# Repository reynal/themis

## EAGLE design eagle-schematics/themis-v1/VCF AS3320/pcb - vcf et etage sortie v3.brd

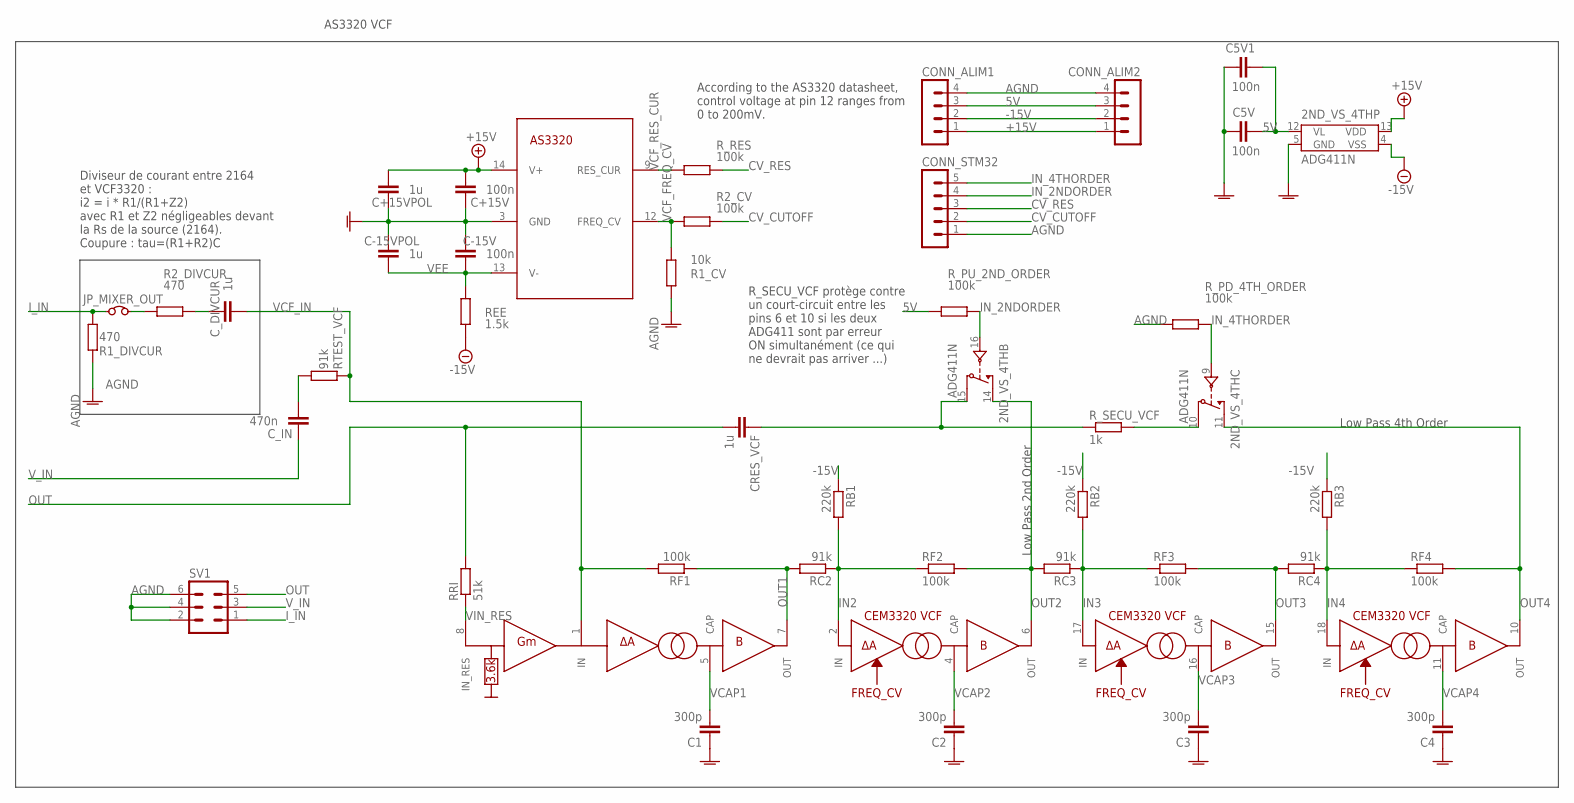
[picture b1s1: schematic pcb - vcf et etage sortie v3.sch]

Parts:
2ND_VS_4TH: ADG411N; DIL16
C1, C2, C3, C4: 300p; C075-032X103
C5V, C5V1: 100n; C075-032X103
C+15V: 100n; C075-032X103
C+15VPOL: 1u; C075-032X103
C-15V: 100n; C075-032X103
C-15VPOL: 1u; C075-032X103
CONN_ALIM1, CONN_ALIM2: MA04-1
CONN_STM32: MA05-1
CRES_VCF: 1u; C075-032X103
C_DIVCUR: 1u; C075-032X103
C_IN: 470n; C075-032X103
JP_MIXER_OUT: JUMPER_WIRE; JUMPER
R1_CV: 10k; 0204/7
R1_DIVCUR, R2_DIVCUR: 470; 0207/10
R2_CV: 100k; 0204/7
RB1: 220k; 0207/10
RB2, RB3: 220k; 0204/7
RC2, RC3, RC4: 91k; 0204/7
REE: 1.5k; 0207/10
RF1, RF3: 100k; 0207/10
RF2, RF4: 100k; 0204/7
RRI: 51k; 0207/10
RTEST_VCF: 91k; 0207/10
R_PD_4TH_ORDER: 100k; 0204/7
R_PU_2ND_ORDER: 100k; 0204/7
R_RES: 100k; 0204/7
R_SECU_VCF: 1k; 0204/7
SV1: MA03-2
VCF: AS3320; DIL18

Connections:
5V: 2ND_VS_4TH.12 (VL), C5V.1, C5V1.1, CONN_ALIM1.3, CONN_ALIM2.3, R_PU_2ND_ORDER.1
+15V: 2ND_VS_4TH.13 (VDD), C+15V.2, C+15VPOL.2, CONN_ALIM1.1, CONN_ALIM2.1, VCF.14 (V+)
-15V: 2ND_VS_4TH.4 (VSS), CONN_ALIM1.2, CONN_ALIM2.2, RB1.1, RB2.1, RB3.1, REE.1
AGND: 2ND_VS_4TH.5 (GND), C1.1, C2.1, C3.1, C4.1, C5V.2, C5V1.2, C+15V.1, C+15VPOL.1, C-15V.2, C-15VPOL.2, CONN_ALIM1.4, CONN_ALIM2.4, CONN_STM32.1, R1_CV.2, R1_DIVCUR.2, R_PD_4TH_ORDER.1, SV1.2, SV1.4, SV1.6, VCF.3 (GND)
CV_CUTOFF: CONN_STM32.2, R2_CV.2
CV_RES: CONN_STM32.3, R_RES.2
IN2: RB1.2, RC2.1, RF2.1, VCF.2 (IN)
IN3: RB2.2, RC3.1, RF3.1, VCF.17 (IN)
IN4: RB3.2, RC4.1, RF4.1, VCF.18 (IN)
IN_2NDORDER: 2ND_VS_4TH.16 (IN), CONN_STM32.4, R_PU_2ND_ORDER.2
IN_4THORDER: 2ND_VS_4TH.9 (IN), CONN_STM32.5, R_PD_4TH_ORDER.2
I_IN: JP_MIXER_OUT.1, R1_DIVCUR.1, SV1.1
unnamed: C_IN.1, RTEST_VCF.1
unnamed: 2ND_VS_4TH.15 (D), CRES_VCF.1, R_SECU_VCF.1
unnamed: 2ND_VS_4TH.10 (D), R_SECU_VCF.2
unnamed: C_DIVCUR.2, R2_DIVCUR.1
unnamed: JP_MIXER_OUT.2, R2_DIVCUR.2
OUT: CRES_VCF.2, RRI.2, SV1.5
OUT1: RC2.2, RF1.1, VCF.7 (OUT)
OUT2: 2ND_VS_4TH.14 (S), RC3.2, RF2.2, VCF.6 (OUT)
OUT3: RC4.2, RF3.2, VCF.15 (OUT)
OUT4: 2ND_VS_4TH.11 (S), RF4.2, VCF.10 (OUT)
VCAP1: C1.2, VCF.5 (CAP)
VCAP2: C2.2, VCF.4 (CAP)
VCAP3: C3.2, VCF.16 (CAP)
VCAP4: C4.2, VCF.11 (CAP)
VCF_FREQ_CV: R1_CV.1, R2_CV.1, VCF.12 (FREQ_CV)
VCF_IN: C_DIVCUR.1, RF1.2, RTEST_VCF.2, VCF.1 (IN)
VCF_RES_CUR: R_RES.1, VCF.9 (RES_CUR)
VEE: C-15V.1, C-15VPOL.1, REE.2, VCF.13 (V-)
VIN_RES: RRI.1, VCF.8 (IN_RES)
V_IN: C_IN.2, SV1.3

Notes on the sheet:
According to the AS3320 datasheet, control voltage at pin 12 ranges from 0 to 200mV.
Diviseur de courant entre 2164 et VCF3320 : i2 = i * R1/(R1+Z2) avec R1 et Z2 négligeables devant la Rs de la source (2164). Coupure : tau=(R1+R2)C
AS3320 VCF
R_SECU_VCF protège contre un court-circuit entre les pins 6 et 10 si les deux ADG411 sont par erreur ON simultanément (ce qui ne devrait pas arriver ...)
Low Pass 2nd Order
Low Pass 4th Order

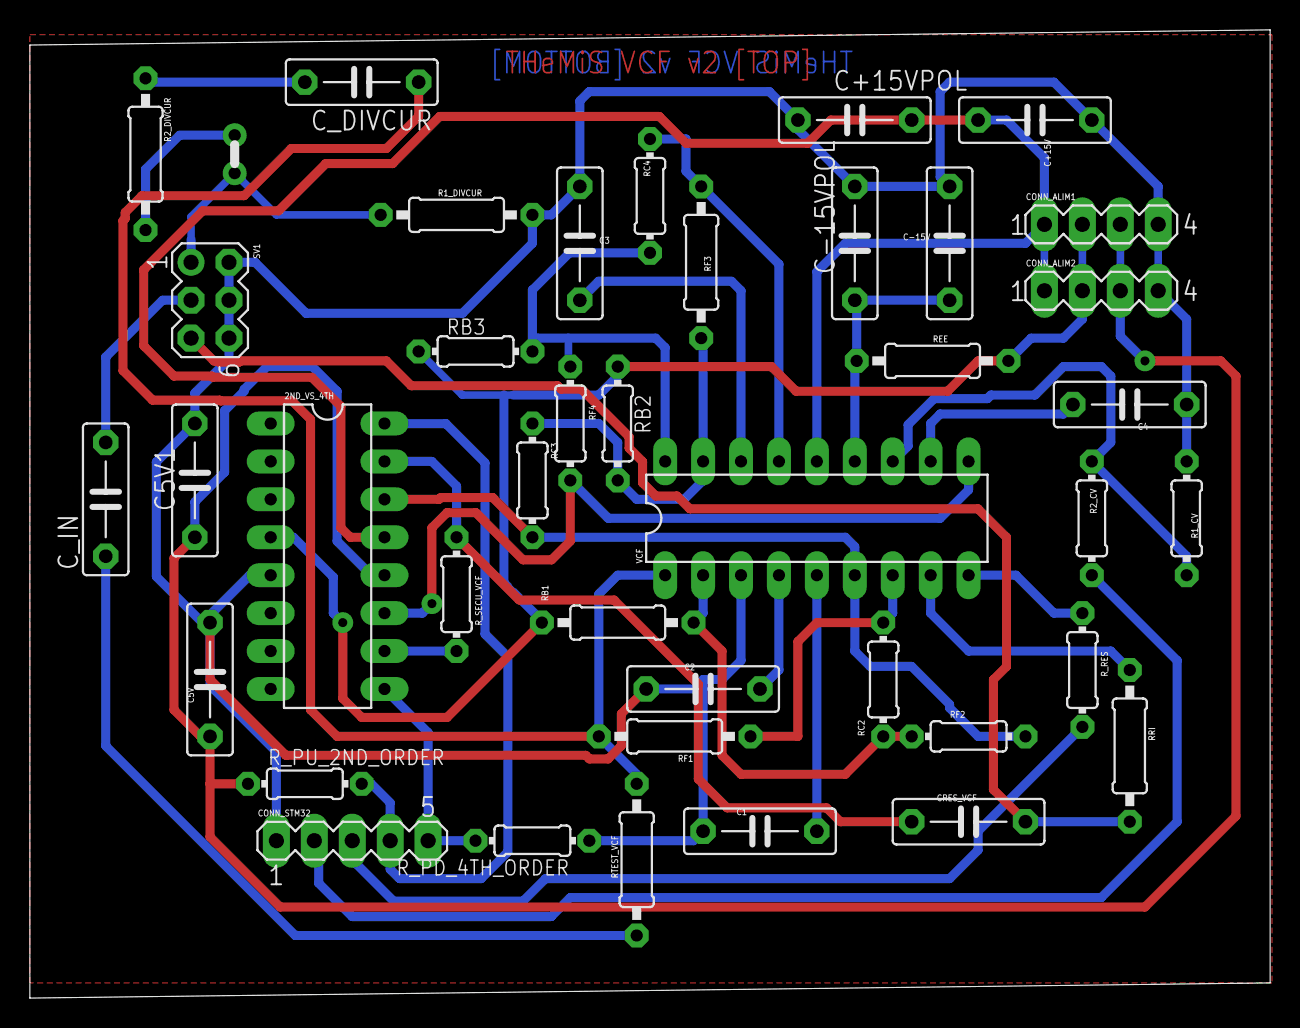
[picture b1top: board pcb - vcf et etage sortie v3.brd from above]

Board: 2 copper layers, 83.1 x 64.8 mm, 41 parts (0 on the bottom side), 32 nets.

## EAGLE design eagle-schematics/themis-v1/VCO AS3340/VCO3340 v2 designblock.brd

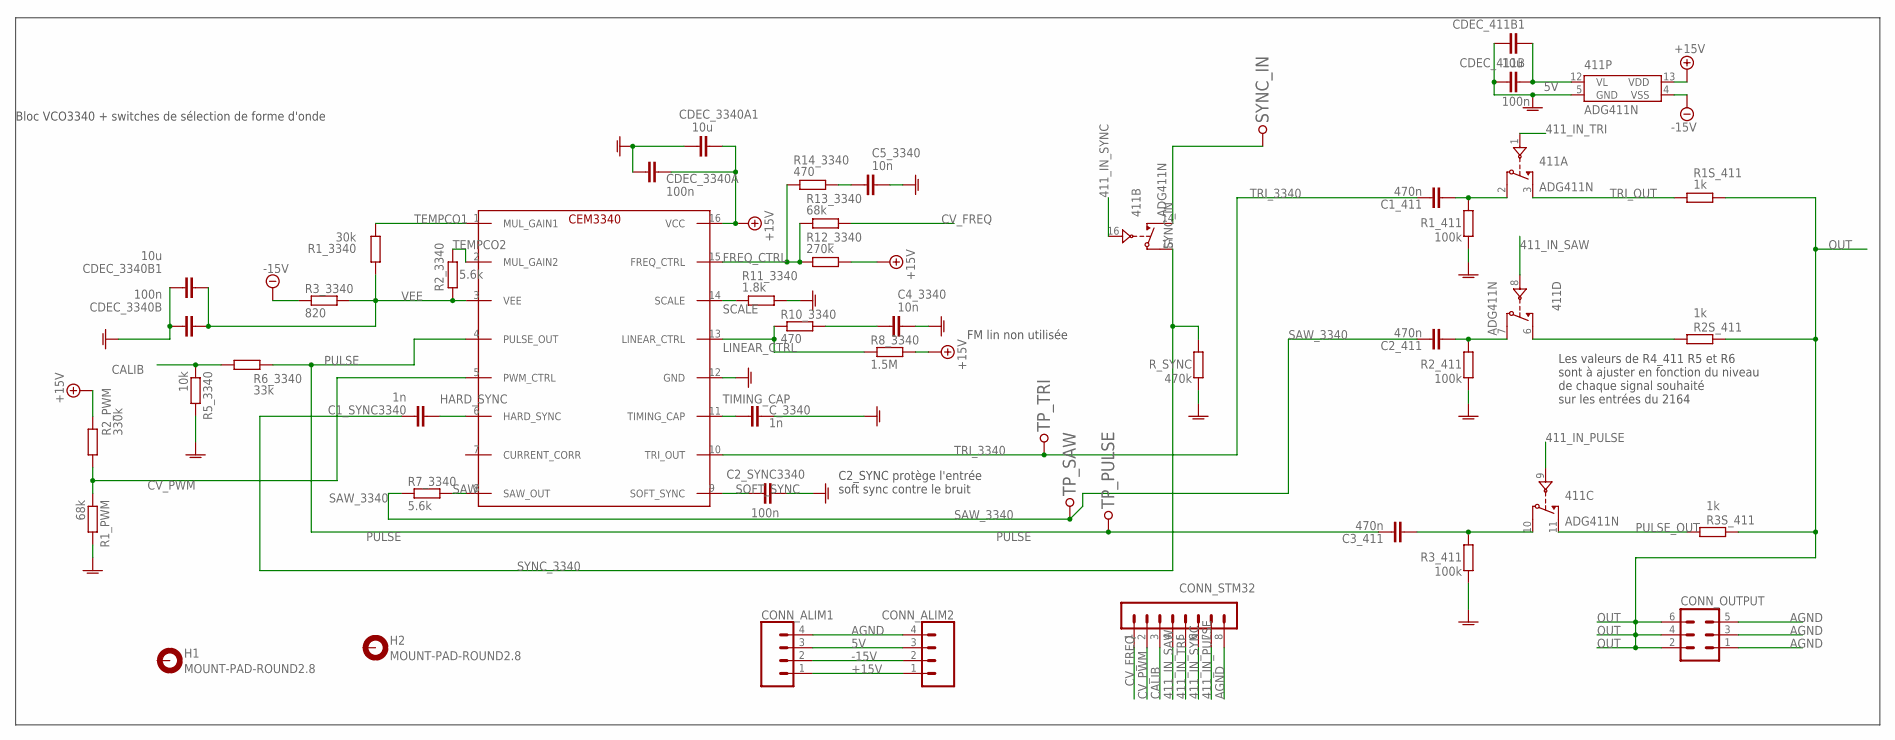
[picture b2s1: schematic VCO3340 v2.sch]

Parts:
411: ADG411N; DIL16
C1_411, C2_411: 470n; C075-032X103
C1_SYNC3340: 1n; C075-032X103
C2_SYNC3340: 100n; C075-032X103
C3_411: 470n; C102-043X133
C4_3340: 10n; C050-025X075
C5_3340: 10n; C075-032X103
CDEC_411B, CDEC_3340A, CDEC_3340B: 100n; C050-025X075
CDEC_411B1, CDEC_3340A1, CDEC_3340B1: 10u; C050-025X075
CEM3340: CEM3340; DIL16
CONN_ALIM1, CONN_ALIM2: CONN_04; 1X04
CONN_OUTPUT: MA03-2
CONN_STM32: MA08-1
C_3340: 1n; C050-025X075
H1, H2: MOUNT-PAD-ROUND2.8; 2,8-PAD
R1S_411, R3S_411: 1k; 0204/7
R1_411, R2_411: 100k; 0207/10
R1_3340: 30k; 0204/7
R1_PWM: 68k; 0207/12
R2S_411: 1k; 0207/10
R2_3340: 5.6k; 0204/7
R2_PWM: 330k; 0204/7
R3_411: 100k; 0204/7
R3_3340: 820; 0204/7
R5_3340: 10k; 0204/7
R6_3340: 33k; 0204/7
R7_3340: 5.6k; 0207/10
R8_3340: 1.5M; 0204/7
R10_3340, R14_3340: 470; 0204/7
R11_3340: 1.8k; 0204/7
R12_3340: 270k; 0204/7
R13_3340: 68k; 0204/7
R_SYNC: 470k; 0204/7
SYNC_IN: TESTPOINT; TESTPOINT_63
TP_PULSE: TESTPOINT; TESTPOINT_63
TP_SAW: TESTPOINT; TESTPOINT_63
TP_TRI: TESTPOINT; TESTPOINT_63

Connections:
5V: 411.12 (VL), CDEC_411B.1, CDEC_411B1.1, CONN_ALIM1.3, CONN_ALIM2.3
411_IN_PULSE: 411.8 (IN), CONN_STM32.4
411_IN_SAW: 411.9 (IN), CONN_STM32.7
411_IN_SYNC: 411.16 (IN), CONN_STM32.6
411_IN_TRI: 411.1 (IN), CONN_STM32.5
+15V: 411.13 (VDD), CDEC_3340A.2, CDEC_3340A1.2, CEM3340.16 (VCC), CONN_ALIM1.1, CONN_ALIM2.1, R2_PWM.2, R8_3340.2, R12_3340.2
-15V: 411.4 (VSS), CONN_ALIM1.2, CONN_ALIM2.2, R3_3340.1
CALIB: CONN_STM32.3, R5_3340.1, R6_3340.1
CV_FREQ: CONN_STM32.1, R13_3340.2
CV_PWM: CEM3340.5 (PWM_CTRL), CONN_STM32.2, R1_PWM.1, R2_PWM.1
unnamed: C2_SYNC3340.2, CEM3340.9 (SOFT_SYNC)
unnamed: 411.6 (S), R2S_411.2
unnamed: C1_SYNC3340.2, CEM3340.6 (HARD_SYNC)
unnamed: CEM3340.1 (MUL_GAIN1), R1_3340.1
unnamed: CEM3340.2 (MUL_GAIN2), R2_3340.1
unnamed: CEM3340.13 (LINEAR_CTRL), R8_3340.1, R10_3340.1
unnamed: CEM3340.8 (SAW_OUT), R7_3340.2
unnamed: CDEC_3340B.2, CDEC_3340B1.2, CEM3340.3 (VEE), R1_3340.2, R2_3340.2, R3_3340.2
unnamed: CEM3340.15 (FREQ_CTRL), R12_3340.1, R13_3340.1, R14_3340.1
unnamed: C5_3340.2, R14_3340.2
unnamed: CEM3340.14 (SCALE), R11_3340.1
unnamed: C4_3340.1, R10_3340.2
unnamed: CEM3340.11 (TIMING_CAP), C_3340.2
unnamed: 411.2 (D), C1_411.2, R1_411.2
unnamed: 411.7 (D), C2_411.2, R2_411.2
unnamed: 411.10 (D), C3_411.2, R3_411.2
OUT: CONN_OUTPUT.2, CONN_OUTPUT.4, CONN_OUTPUT.6, R1S_411.2, R2S_411.1, R3S_411.1
PULSE_OUT: 411.11 (S), R3S_411.2
SAW_3340: C2_411.1, R7_3340.1, TP_SAW.P$1
SYNC_3340: 411.15 (D), C1_SYNC3340.1, R_SYNC.2
SYNC_IN: 411.14 (S), SYNC_IN.P$1
TRI_3340: C1_411.1, CEM3340.10 (TRI_OUT), TP_TRI.P$1
TRI_OUT: 411.3 (S), R1S_411.1

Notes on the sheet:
Bloc VCO3340 + switches de sélection de forme d'onde
Les valeurs de R4_411 R5 et R6 sont à ajuster en fonction du niveau de chaque signal souhaité sur les entrées du 2164
C2_SYNC protège l'entrée soft sync contre le bruit
FM lin non utilisée

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
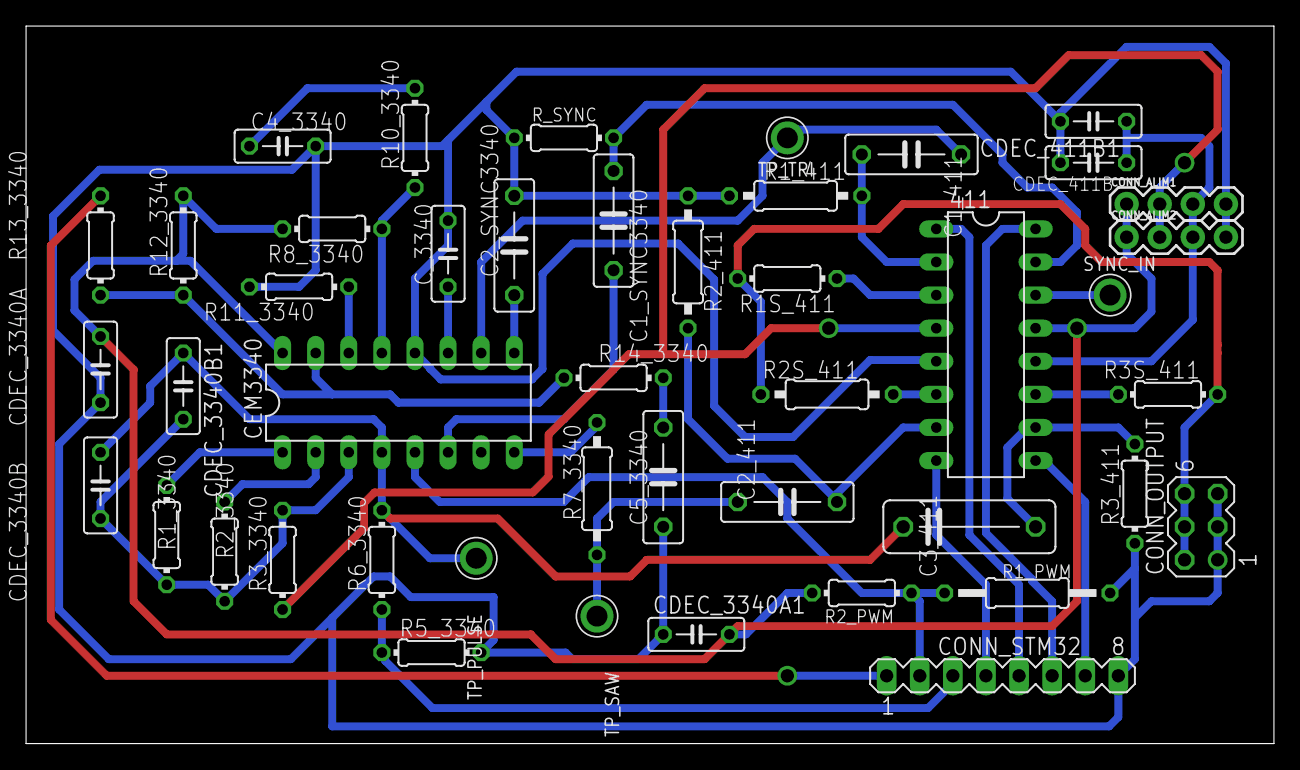
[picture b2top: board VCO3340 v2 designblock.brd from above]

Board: 2 copper layers, 95.8 x 55.1 mm, 45 parts (0 on the bottom side), 35 nets.

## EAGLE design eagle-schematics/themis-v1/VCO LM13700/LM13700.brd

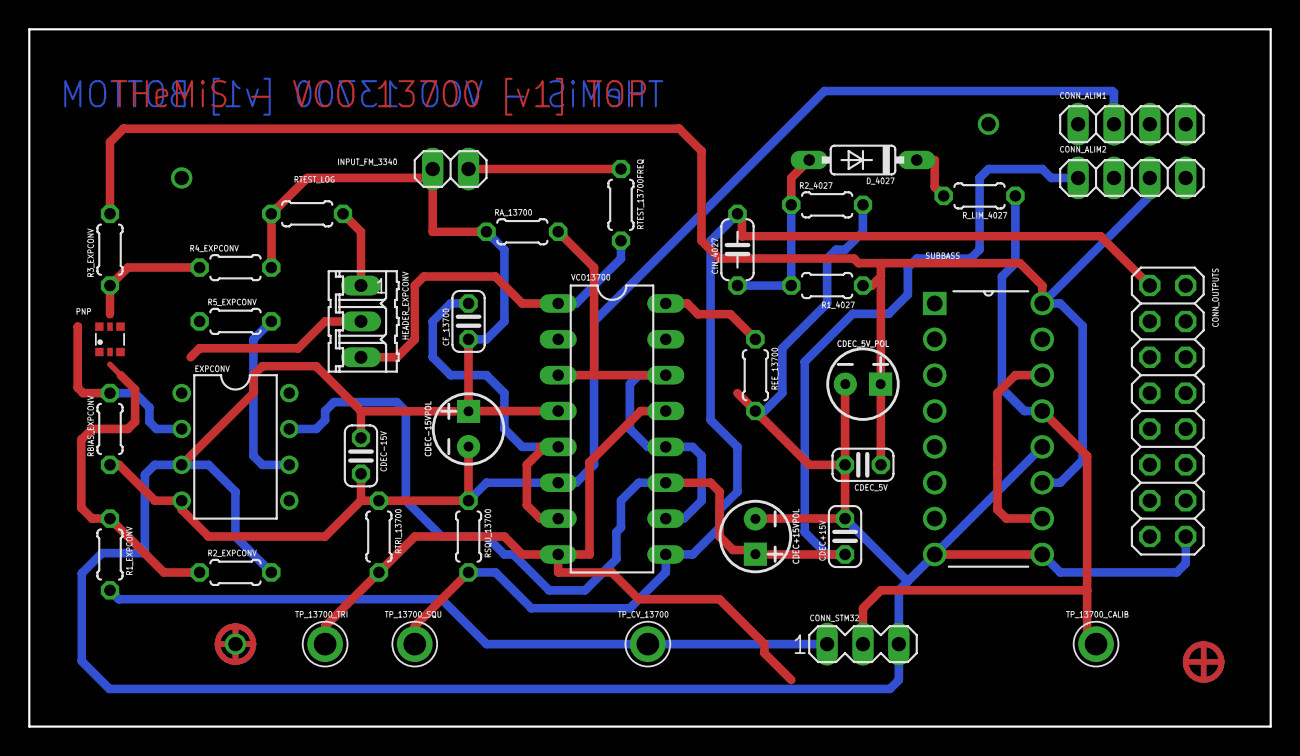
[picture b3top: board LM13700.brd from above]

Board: 2 copper layers, 87.9 x 49.4 mm, 38 parts (0 on the bottom side), 24 nets.

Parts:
CDEC+15V: 100n; C025-024X044
CDEC+15VPOL: 10uF; CPOL-RADIAL-2.5MM-5MM-KIT
CDEC-15V: 100n; C025-024X044
CDEC-15VPOL: 10uF; CPOL-RADIAL-2.5MM-5MM-KIT
CDEC_5V: 100n; C025-024X044
CDEC_5V_POL: 10uF; CPOL-RADIAL-2.5MM-5MM-KIT
CF_13700: 100nF; C025-024X044
CIN_4027: 470n; C050-024X044
CONN_ALIM1, CONN_ALIM2: 1X04
CONN_OUTPUTS: 2X08
CONN_STM32: MA03-1
D_4027: 1N4148DO35-7; DO35-7
EXPCONV: TL081; DIL08
HEADER_EXPCONV: 03P
INPUT_FM_3340: 1X02
PNP: BC857BS; SOT363
R1_4027, R2_4027: 100k; 0204/5
R1_EXPCONV: 330; 0204/5
R2_EXPCONV, R4_EXPCONV: 10; 0204/5
R3_EXPCONV: 260; 0204/5
R5_EXPCONV: 110; 0204/5
RA_13700: 4.7k; 0204/5
RBIAS_EXPCONV: 47k; 0204/5
REE_13700: 27k; 0204/5
RSQU_13700: 10k; 0204/5
RTEST_13700FREQ: 27k; 0204/5
RTEST_LOG: 1k; 0204/5
RTRI_13700: 12k; 0204/5
R_LIM_4027: 1k; 0204/5
SUBBASS: HEF4027BP; DIP254P762X420-16
TP_13700_CALIB, TP_13700_SQU, TP_13700_TRI: TESTPOINT_63
TP_CV_13700: TESTPOINT_63
VCO13700: LM13700N; DIL16

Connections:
5V: CDEC_5V.1, CDEC_5V_POL.1, CONN_ALIM1.3, CONN_ALIM2.3, R1_4027.1, R3_EXPCONV.2, SUBBASS.11, SUBBASS.16
+15V: CDEC+15V.1, CDEC+15VPOL.1, CONN_ALIM1.1, CONN_ALIM2.1, EXPCONV.7, VCO13700.11
-15V: CDEC-15V.2, CDEC-15VPOL.2, CONN_ALIM1.2, CONN_ALIM2.2, EXPCONV.4, RBIAS_EXPCONV.1, RSQU_13700.1, RTRI_13700.1, VCO13700.6
AGND: CDEC+15V.2, CDEC+15VPOL.2, CDEC-15V.1, CDEC-15VPOL.1, CDEC_5V.2, CDEC_5V_POL.2, CF_13700.1, CONN_ALIM1.4, CONN_ALIM2.4, CONN_OUTPUTS.2, CONN_OUTPUTS.4, CONN_OUTPUTS.6, CONN_OUTPUTS.8, CONN_OUTPUTS.10, CONN_OUTPUTS.12, CONN_OUTPUTS.14, CONN_OUTPUTS.16, CONN_STM32.3, EXPCONV.3, INPUT_FM_3340.2, R2_4027.2, R2_EXPCONV.2, R4_EXPCONV.2, RA_13700.1, REE_13700.2, RTEST_LOG.2, SUBBASS.8, SUBBASS.9, SUBBASS.12, VCO13700.4
BIAS_4027: CIN_4027.1, D_4027.A, R1_4027.2, R2_4027.1
CALIB_13700: CONN_STM32.2, R_LIM_4027.1, SUBBASS.13, TP_13700_CALIB.P$1
CV_FREQ_13700: CONN_STM32.1, R1_EXPCONV.2, TP_CV_13700.P$1
FM_ENTREE_13700: HEADER_EXPCONV.3, RTEST_13700FREQ.2, VCO13700.1
IA: REE_13700.1, VCO13700.16
INPUT_FM_3340: INPUT_FM_3340.1, RTEST_13700FREQ.1
unnamed: SUBBASS.10, SUBBASS.14
unnamed: D_4027.C, R_LIM_4027.2
unnamed: EXPCONV.6, R5_EXPCONV.2
unnamed: RA_13700.2, VCO13700.3, VCO13700.10, VCO13700.12, VCO13700.14
unnamed: CF_13700.2, VCO13700.5, VCO13700.7
unnamed: HEADER_EXPCONV.1, RTEST_LOG.1
OUT_EXPCONV: HEADER_EXPCONV.2, PNP.3
PNP1_B: PNP.2, R1_EXPCONV.1, R2_EXPCONV.1
PNP1_C: EXPCONV.2, PNP.6, RBIAS_EXPCONV.2
PNP2_B: PNP.5, R3_EXPCONV.1, R4_EXPCONV.1
PNP_E: PNP.1, PNP.4, R5_EXPCONV.1
SQU_13700: CIN_4027.2, CONN_OUTPUTS.1, CONN_OUTPUTS.3, CONN_OUTPUTS.5, CONN_OUTPUTS.7, RSQU_13700.2, TP_13700_SQU.P$1, VCO13700.9
SUB_OUT: CONN_OUTPUTS.9, CONN_OUTPUTS.11, SUBBASS.15
TRI_13700: CONN_OUTPUTS.13, CONN_OUTPUTS.15, RTRI_13700.2, TP_13700_TRI.P$1, VCO13700.8, VCO13700.13

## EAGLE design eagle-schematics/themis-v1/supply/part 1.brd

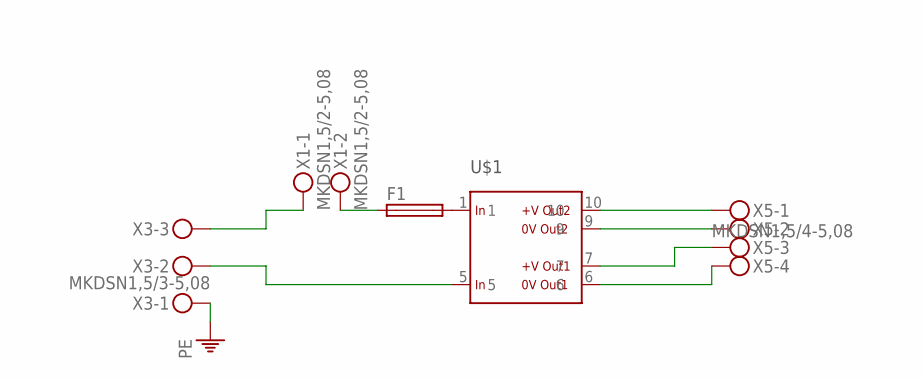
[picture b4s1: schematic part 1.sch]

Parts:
F1: SH22,5A
U$1: DOUBLE_ISO; 2ISO
X1: MKDSN1,5/2-5,08
X3: MKDSN1,5/3-5,08
X5: MKDSN1,5/4-5,08

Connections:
unnamed: U$1.6, X5.4
unnamed: F1.1, X1.2
unnamed: U$1.7, X5.3
unnamed: F1.2, U$1.1
unnamed: U$1.9, X5.2
unnamed: X1.1, X3.3
unnamed: U$1.10, X5.1
unnamed: U$1.5, X3.2
PE: X3.1

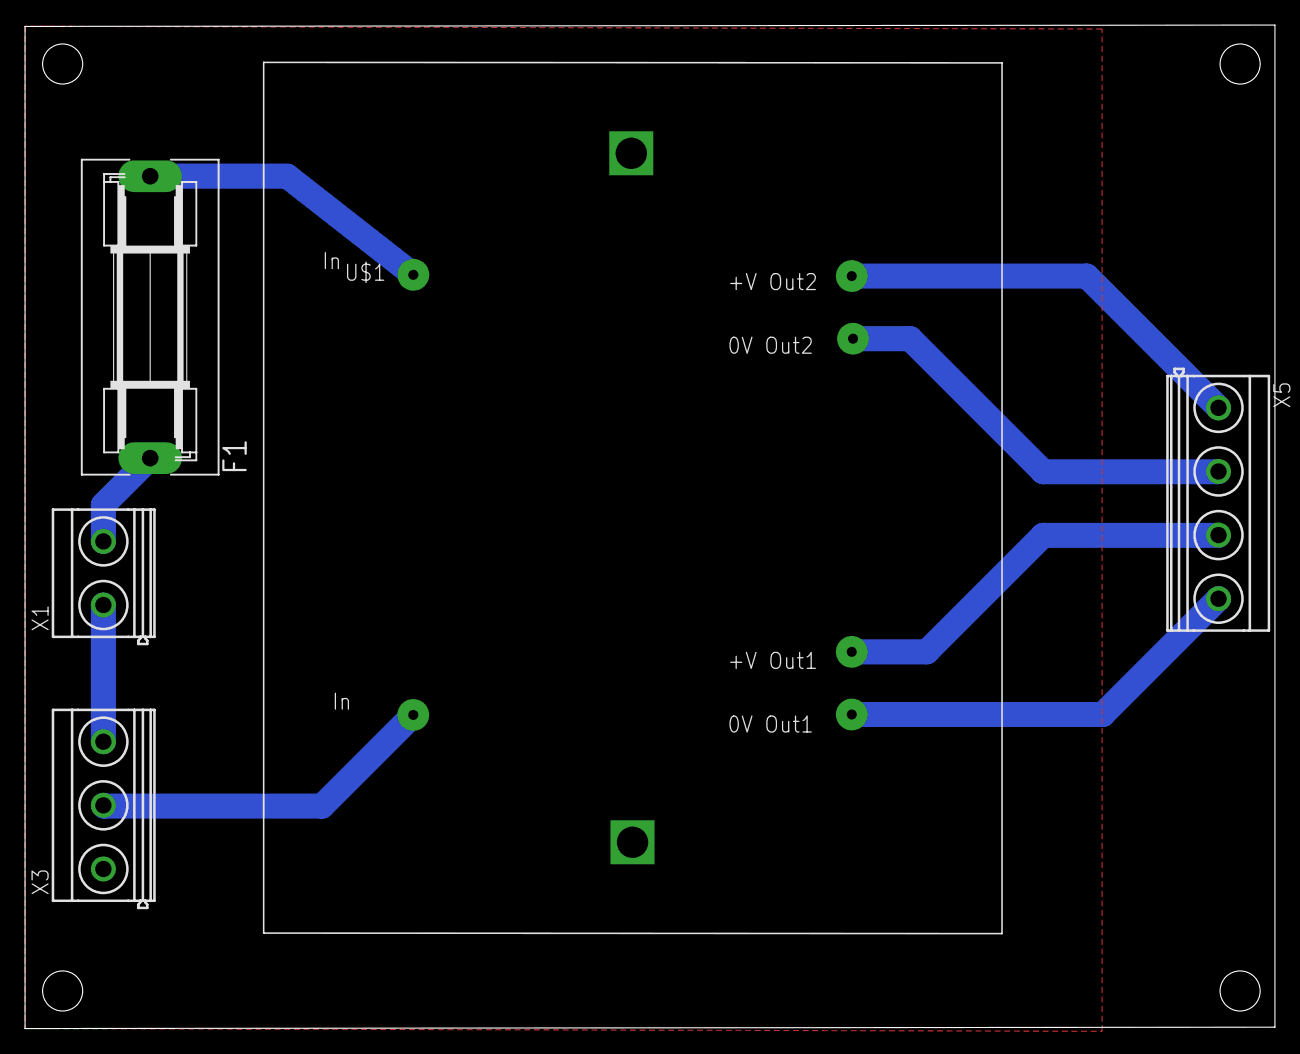
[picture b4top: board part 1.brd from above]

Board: 2 copper layers, 99.8 x 80.1 mm, 5 parts (0 on the bottom side), 8 nets.

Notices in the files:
parts and their libraries:
SparkFun-Connectors: Licensing: Creative Commons ShareAlike 4.0 International - https://creativecommons.org/licenses/by-sa/4.0
